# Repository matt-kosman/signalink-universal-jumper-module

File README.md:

# SignaLink Universal Jumper Module
 The SignaLink Universal Jumper Module is a DIY accessory for the Tigertronics SignaLink amateur radio sound card. The jumper includes all of the circuit components needed to connect handheld radios with a combined MIC/PTT line, and it provides a consistent pinout for building custom cables. 
 
 The module is licensed under the TAPR Open Hardware License [www.tapr.org/OHL](http://www.tapr.org/OHL). 

# Narrative
The SignaLink by Tigertronics is a popular and convenient USB sound card for amateur radio. It has a user-configurable RJ-45 connector for interfacing with many different systems. Users change the connector pinout to suit their radio and cable. See the Tigertronics [Wiring Information](http://www.tigertronics.com/sl_wirebm.htm) and [Detailed Jumper Installation Procedure](http://www.tigertronics.com/files/signalink_jumper_procedure.pdf). 

When used with a single radio - especially a radio with an RJ-45 input - Tigertronics' instructions are simple and effective. Users also have the option of purchasing a turnkey solution with pre-installed jumper and custom cable. 

Homebrewers or amateurs with multiple radios, however, may find themselves needing to change configurations often. Opening the SignaLink case can be inconvenient. Further, interfacing with handheld radios - which may have a combination MIC/PTT line - adds complexity because of the extra circuit components. 

The Universal Jumper has two main purposes:
1. It includes all of the circuitry needed to interface with combined MIC/PTT handheld radios and it passes through MIC and PTT signals separately. 
2. It provides a consistent pinout for users who need to design custom cables anyway. 

The Universal Jumper is likely not useful for amateurs with a single radio configuration or who change configurations infrequently. 

I designed the Universal Jumper to work with my Yaesu VX-3 and uBitx, so that I can switch between the two just by changing the cable. 

If indeed this is a problem that needs solving, there are certainly other ways to solve it. This jumper is a solution that works for me; and it was a fun, simple project to design and build. I'm sharing it here with the hope that it helps you, too.  

This project is provided as-is and without any warranty, in accordance with its license. You are responsible for verifying that the jumper will work with your radios and cables. 

# Design
## MIC/PTT Interface
The main element in the design is the interface to handheld radios, which have a combination MIC/PTT line, in contrast to the separate lines used by mobile and base station radios. 

In simple terms, MIC can be considered AC and the PTT DC. One solution to separate the two is an RC-type filter, or, expressed differently, a DC-blocking capacitor and a current-limiting resistor. Tigertronics provides a reference circuit on their [website](http://www.tigertronics.com/sl_wireht_comb.htm) which addresses this type of connection. 

<p align="center"></br><b>MIC/PTT Interface</b></p>

Component values can also be adjusted to accommodate a particular radio or in general; values within the same order or magnitude should work similarly. 

## SignaLink Interface
Inside the enclosure, an 8x2 rounded pin DIP socket sits between the SignaLink circuitry and the RJ-45 external connector. 

<p align="center"></br><b>SignaLink PCB Showing JP1 Socket for Universal Jumper</b></p>

The socket can be used with off-the-shelf jumper modules or hand wired by the end user. The Universal Jumper will also fit into this socket, using standard 0.1-inch pitch rounded pins, with the two rows separated by 0.3 inches. 

<p align="center"></br><b>SignaLink Interface and Passthrough</b></p>

The universal jumper passes all signals - SPK, MIC, and PTT - through to the RJ45 in addition to routing them to the HT interface circuit. The universal jumper also passes through PWR to support the legacy SignaLink SL-1+ (non-USB). 

# Build

<p align="center"></br><b>Completed Build, THT and SMD Versions</b></p>

## Schematic
The schematic consists of both of the above elements, plus an additional set of resistor and capacitor which allow the user to choose a through hole or surface mount assembly on the same PCB. 

The schematic is available as a [PDF](kicad/pdf/schematic.pdf) in this folder and as part of the KiCAD project. 

## PCB

The jumper PCB accommodates both through hole and surface mount components and provides the correct spacing to interface with the SignaLink. 

<p align="center"></br><b>PCB Design in KiCAD</b></p>

The PCB can also be ordered using the KiCAD project files or included gerbers from a number of manufacturers, including OshPark, where the prototypes were made. [Click here](https://oshpark.com/shared_projects/eV0r6j4w) to easily order the PCBs from OshPark. 

<p align="center"></br><b>Unpopulated Boards from OshPark</b></p>

The jumper can also be constructed without a PCB by using standard 0.1-inch spaced perfboard. Place the J1 and J2 connectors 0.3 inches apart; that is, there are two rows between the connectors.

## BOM
To make the project more usable for the community, the PCB offers a choice between surface mount and through hole is designed to work with spare parts to the extent possible. **Populate only one capacitor and one resistor.** 

Similar values and packages may be substituted. Always verify that the chosen values are compatible with the connected radio prior to power on. The example build below uses approximate values and packages, namely 2kOhm resistors and one 0603 SMD package. 

<p align="center"></br><b>SMD and THT Versions Ready to Build</b></p>

In case components need to be purchased, the included [BOM_surface-mount.csv](bom/BOM_surface-mount.csv) and [BOM_through-hole.csv](bom/BOM_through-hole.csv) give examples of acceptable parts. Either can be imported into DigiKey. 

Reference | Quantity | Value | Package
--------- | -------: | ----: | ----
J1, J2 | 2 | 0.018-inch diameter Rounded Header Pin | 0.1-inch, 1x8-position
C1 | 0 or 1 | 0.1u | SMD, 0805
R1 | 0 or 1 | 2.7k | SMD, 0805
C2 | 0 or 1 | 0.1u | THT Radial, 2.5mm pitch
R2 | 0 or 1 | 2.7k | THT Axial, 6.3mm max.

**Note in particular that J1 and J2 must use round pin headers - square headers will damage the SignaLink.**

## Cabling
**Custom cables are required.** Standard RJ-45 terminated CAT5 cables are unlikely to be compatible with any radio. Cables purchased from Tigertronics are also not compatible. Refer to the radio manual and the reference below for pinouts for building cables. 

# Reference

<p align="center"></br><b>Installed Jumper with Pinout Reference</b></p>

# Known Issues

**Silkscreen Text** The license URL on the back of the board is too small.

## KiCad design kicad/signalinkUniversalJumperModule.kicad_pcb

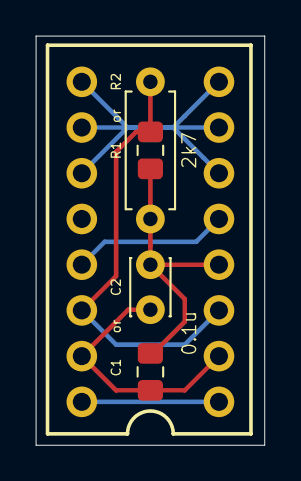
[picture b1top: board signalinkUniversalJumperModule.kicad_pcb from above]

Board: 2 copper layers, 12.7 x 22.7 mm, 6 parts (0 on the bottom side), 6 nets.

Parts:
C1: 0.1u; C_0805_2012Metric_Pad1.15x1.40mm_HandSolder
C2: 0.1u; C_Disc_D3.0mm_W2.0mm_P2.50mm
J1: Signalink; PinHeader_1x08_P2.54mm_Vertical
J2: RJ45; PinHeader_1x08_P2.54mm_Vertical
R1: 2k7; R_0805_2012Metric_Pad1.15x1.40mm_HandSolder
R2: 2k7; R_Axial_DIN0207_L6.3mm_D2.5mm_P7.62mm_Horizontal

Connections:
/GND: J1.1, J1.2, J1.3, J2.6, J2.7, J2.8
/HT: C1.1, C2.1, J2.4, R1.1, R2.1
/MIC: C1.2, C2.2, J1.7, J2.2
/PTT: J1.6, J2.3, R1.2, R2.2
/PWR: J1.5, J2.5
/SPK: J1.8, J2.1

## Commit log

2019-10-02 Initial commit
    Initial commit. README is in work. Boards to be ordered, populated, and tested.
2019-10-20 Added images of completed build
2019-10-21 Remove kicad images
2019-10-21 Add kicad images
2019-10-21 Change image sizes
2019-10-21 Fixed image sizes
